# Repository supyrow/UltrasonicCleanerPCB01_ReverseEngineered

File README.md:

# UltrasonicCleanerPCB01_ReverseEngineered
40kHz transducer driver

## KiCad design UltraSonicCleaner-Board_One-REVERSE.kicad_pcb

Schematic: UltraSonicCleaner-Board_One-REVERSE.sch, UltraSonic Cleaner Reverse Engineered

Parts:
C1, C2: C; C_Rect_L18.0mm_W5.0mm_P15.00mm_FKS3_FKP3
C3: Varistor; RV_Disc_D21.5mm_W4.3mm_P10mm
C4, C5: 1000uF @ 25V; CP_Radial_D10.0mm_P5.00mm
C6: DNP; C_Rect_L24.0mm_W7.0mm_P22.50mm_MKT
C7, C8, C14, C15: 100nF; C_Disc_D5.1mm_W3.2mm_P5.00mm
C9, C10: 330nF @ 400V; C_Rect_L11.0mm_W5.3mm_P10.00mm_MKT
C11, C12: 105j630v; C_Rect_L26.5mm_W11.5mm_P22.50mm_MKS4
C13: 2nF @ 2000v; C_Rect_L18.0mm_W5.0mm_P15.00mm_FKS3_FKP3
D1, D2, D3, D4, D7, D8, D9, D10, D11, D12: 1N4007; D_DO-41_SOD81_P10.16mm_Horizontal
D5, D6: FR157; D_DO-41_SOD81_P12.70mm_Horizontal
F1, F2: Fuse; Fuse_Littelfuse-LVR100
F3, F4: Jumper; Fuse_Littelfuse-LVR125
H1, H2, H3, H4: MountingHole; MountingHole_3.2mm_M3
HS1, HS2, HS3: Heatsink; HEATSINK_15x10x25mm
J1, J2: N; Connector_Tab_Pitch5.08mm_Drill1.3mm
J3: L; Connector_Tab_Pitch5.08mm_Drill1.3mm
J4: PTC; Connector_Tab_Pitch5.08mm_Drill1.3mm
J5: NB; Connector_Tab_Pitch5.08mm_Drill1.3mm
J6: LB; Connector_Tab_Pitch5.08mm_Drill1.3mm
J7: CPU_Control; JST_XH_B4B-XH-A_1x04_P2.50mm_Vertical
J8: OUTPUT+; Connector_Tab_Pitch5.08mm_Drill1.3mm
J9: OUTPUT-; Connector_Tab_Pitch5.08mm_Drill1.3mm
K1, K2: LF3F-1A-DC6V; Relay_SPST_SANYOU_SRD_Series_Form_A
L1: L_Coupled; Inductor_Custom_1to1
L2: Transformer_110_220-DG1; Transformer_12pin_23mm_5pp
L3: Transformer_3in1; Inductor_Custom_3x
L4: Transformer_110-SY; Transformer_12pin_23mm_5pp
Q1: L7805CV; TO-220-3_Vertical
R1: 330k @ 0.5W; R_Axial_DIN0309_L9.0mm_D3.2mm_P15.24mm_Horizontal
R3: ?R @ 3W; R_Axial_DIN0614_L14.3mm_D5.7mm_P20.32mm_Horizontal
R4: 24K @ 1W; R_Axial_DIN0411_L9.9mm_D3.6mm_P12.70mm_Horizontal
R5: 24K @ 1W; R_Axial_DIN0411_L9.9mm_D3.6mm_P15.24mm_Horizontal
R6, R7: 510R @ 0.25W; R_Axial_DIN0207_L6.3mm_D2.5mm_P10.16mm_Horizontal
R8, R9: DNP; R_Axial_DIN0309_L9.0mm_D3.2mm_P12.70mm_Horizontal
R12: 5.1R @ 3W; R_Axial_DIN0614_L14.3mm_D5.7mm_P15.24mm_Horizontal
R18, R19: 4.7R @ 0.25W; R_Axial_DIN0207_L6.3mm_D2.5mm_P10.16mm_Horizontal
T1: Transformer_1P_1S; Inductor_Custom_1to1
VQ1, VQ2: FJP13009H2TU; TO-220-3_Vertical

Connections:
+5V: C4.1, C8.1, J7.4, Q1.3 (OUT)
/H: C15.1, J7.1, R18.2
/T: C14.2, J7.2, R19.2
unnamed: C1.1, C3.2, J1.1, J2.1, J5.1, L1.3, R1.2
unnamed: C1.2, C3.1, J6.1, K1.1, L1.1, R1.1
unnamed: C2.1, D3.1, D4.2, L1.4, T1.2 (AB)
unnamed: C2.2, D1.1, D2.2, L1.2
unnamed: C5.1, C7.2, D7.1, D9.1, Q1.1 (IN)
unnamed: C6.1, D2.1, D4.1, R3.2
unnamed: C9.1, L3.2, R6.1
unnamed: C9.2, R4.2, R6.2, VQ1.1 (B)
unnamed: C10.1, L3.3, R7.1
unnamed: C10.2, R5.2, R7.2, VQ2.1 (B)
unnamed: C11.1, C12.1, L4.11, L4.12
unnamed: C11.2, D5.1 (K), R3.1, R4.1, R8.2, VQ1.2 (C)
unnamed: C6.2, C12.2, D1.2, D3.2, D6.2 (A), F3.1, L3.4, R9.1
unnamed: C13.1, J8.1, L2.1, L2.2, L2.3, L2.4, L2.5, L2.6
unnamed: C13.2, J9.1, L3.6, R12.1
unnamed: C4.2, C5.2, C7.1, C8.2, C14.1, C15.2, D8.2, D10.2, D11.2, D12.2, J7.3, K1.2, K2.2, Q1.2 (GND)
unnamed: D5.2 (A), D6.1 (K), F4.1, L3.1, L4.7, R5.1, R8.1, R9.2, VQ2.2 (C)
unnamed: D7.2, D8.1, T1.4 (SB)
unnamed: D9.2, D10.1, T1.3 (SA)
unnamed: D11.1, K1.5, R19.1
unnamed: D12.1, K2.5, R18.1
unnamed: F1.1, J3.1, K2.1
unnamed: F1.2, K1.3, T1.1 (AA)
unnamed: F2.1, J4.1
unnamed: F2.2, K2.3
unnamed: F3.2, VQ2.3 (E)
unnamed: F4.2, VQ1.3 (E)
unnamed: L2.7, L2.8, L2.9, L2.10, L2.11, L2.12, L4.6
unnamed: L3.5, L4.9, R12.2
unnamed: L4.1, L4.2, L4.3, L4.4

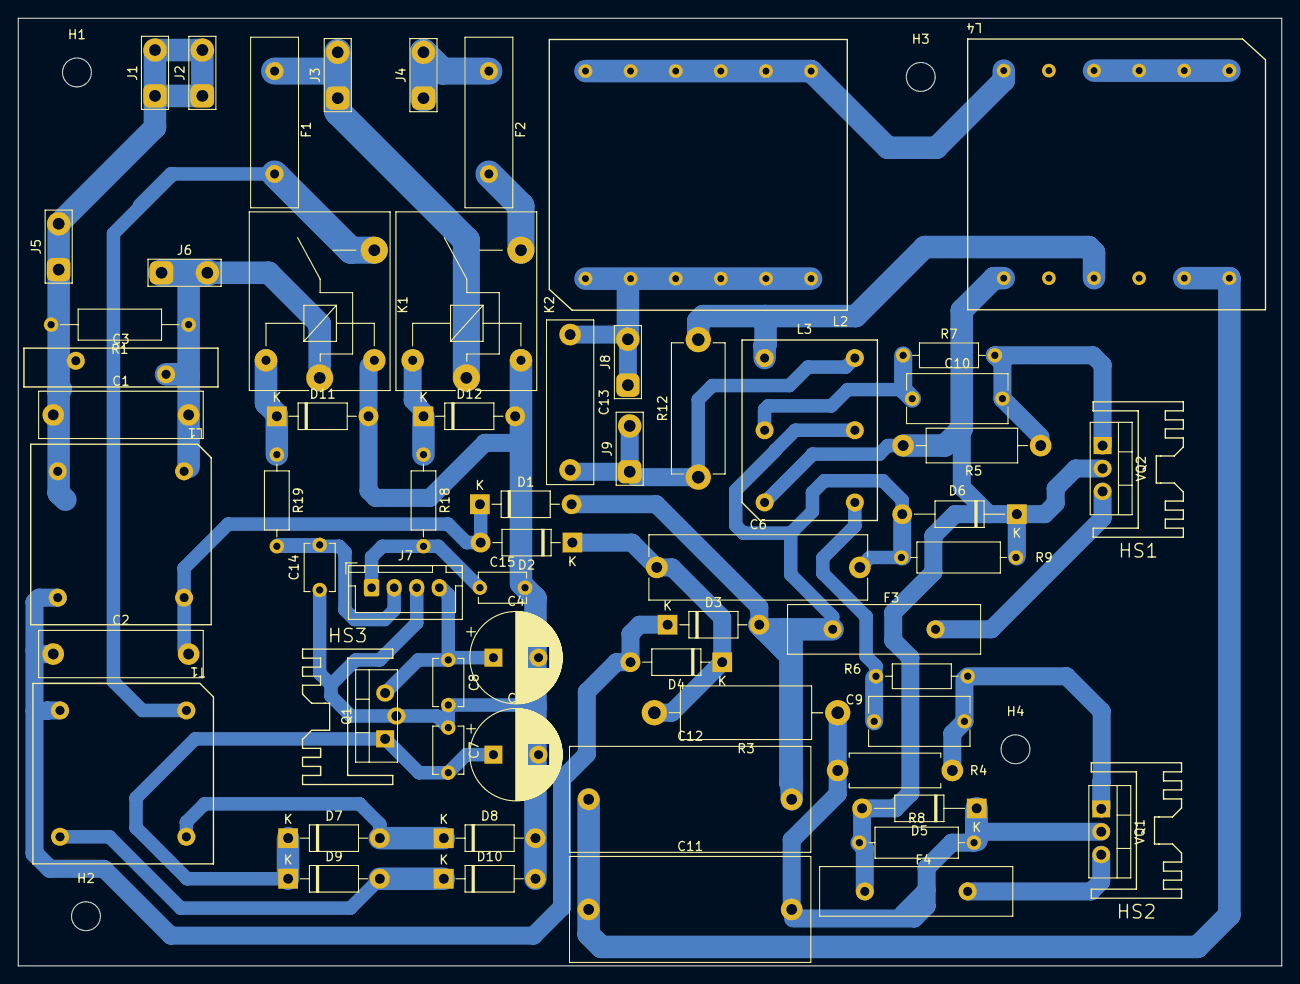
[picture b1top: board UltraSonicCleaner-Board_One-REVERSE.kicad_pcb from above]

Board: 2 copper layers, 140.0 x 105.0 mm, 68 parts (0 on the bottom side), 33 nets.

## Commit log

2021-05-19 Upload of initial design.
